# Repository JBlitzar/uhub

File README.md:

# uhub

> [!NOTE]
> uhh so the ports are very close together, which means for some thick USB connectors, plugging in to ports that are next to each other won't work. You might want to space them out if youre going to fab this yourself. Or, you know, just live with it and use skinny connectors.

## Finished product

## other pictures

## What this project is and why I made it

It's a USB hub. It has one upstream USB-C port, and seven downstream ports: Five USB-A and two USB-C. Since the ICs only support four downstream ports, I daisy-chained two of them.

I wanted to make it to connect to more accessories at a time, for use either on my laptop or with my raspberry pi. I also wanted to make it to level up my PCB design skills, after making a macropad. The routing was considerably more difficult, because there a lot more considerations to be made regarding impedance et al.

## PCB Images

[KiCanvas](https://kicanvas.org/?repo=https%3A%2F%2Fgithub.com%2FJBlitzar%2Fuhub%2Ftree%2Fmain%2FPCB%2Fusbhub)

For-fun PCB plot, kicad screenshots below.

## Credits

USB Hub Guide: https://rudymakes.com/blog/usb-hub/

I'd like to credit this guide, since I used it as reference, but my design is distinct and my own.

## Bom in table format

| Name            | Link                                              | Footprint                        | Quantity | Value            | LCSC Part # | Designator                                                    | Distributor  | Total cost |
| --------------- | ------------------------------------------------- | -------------------------------- | -------- | ---------------- | ----------- | ------------------------------------------------------------- | ------------ | ---------- |
| 1uF capacitor   | https://www.lcsc.com/product-detail/C29266.html   | C0402                            | 13       | 1uF              | C29266      | C11, C13, C15, C17, C19, C20, C21, C22, C23, C24, C25, C7, C9 | LCSC         | 0          |
| 100nF capacitor | https://www.lcsc.com/product-detail/C60474.html   | C0402                            | 6        | 100nF            | C60474      | C12, C14, C16, C18, C26, C27                                  | LCSC         | 0          |
| 5.1k resistor   | https://www.lcsc.com/product-detail/C105872.html  | R0402                            | 6        | 5.1k             | C105872     | R10, R11, R4, R7, R8, R9                                      | LCSC         | 0          |
| USB IC          | https://www.lcsc.com/product-detail/C2684433.html | SSOP-16_L4.6-W2.6-P0.53-LS4.0-BL | 2        | SL2.1S           | C2684433    | U1, U2                                                        | LCSC         | 0          |
| USB C port      | https://www.lcsc.com/product-detail/C2765186.html | USB-C-SMD_TYPE-C-16PIN-2MD-073   | 3        | TYPE-C 16PIN 2MD | C2765186    | USB1_UPSTREAM1, USB5, USB6                                    | LCSC         | 0          |
| USB A port      | https://www.lcsc.com/product-detail/C668591.html  | USB-A-TH_10.0QHHTZB6.3           | 5        | 10.0 QHHTZB6.3   | C668591     | USB2, USB3, USB4, USB7, USB8                                  | LCSC         | 0          |
| PCB             | N/A                                               | N/A                              | 1        | N/A              | N/A         | N/A                                                           | JLCPCB       | 4          |
| PCBA            | N/A                                               | N/A                              | 1        | N/A              | N/A         | N/A                                                           | JLCPCB       | 32.78      |
| Shipping        | N/A                                               | N/A                              | 1        | N/A              | N/A         | N/A                                                           | JLCPCB       | 3.3        |
| Sales tax       | N/A                                               | N/A                              | 1        | N/A              | N/A         | N/A                                                           | JLCPCB       | 4          |
| 3d printed case | N/A                                               | N/A                              | 1        | N/A              | N/A         | N/A                                                           | self-sourced | 0          |

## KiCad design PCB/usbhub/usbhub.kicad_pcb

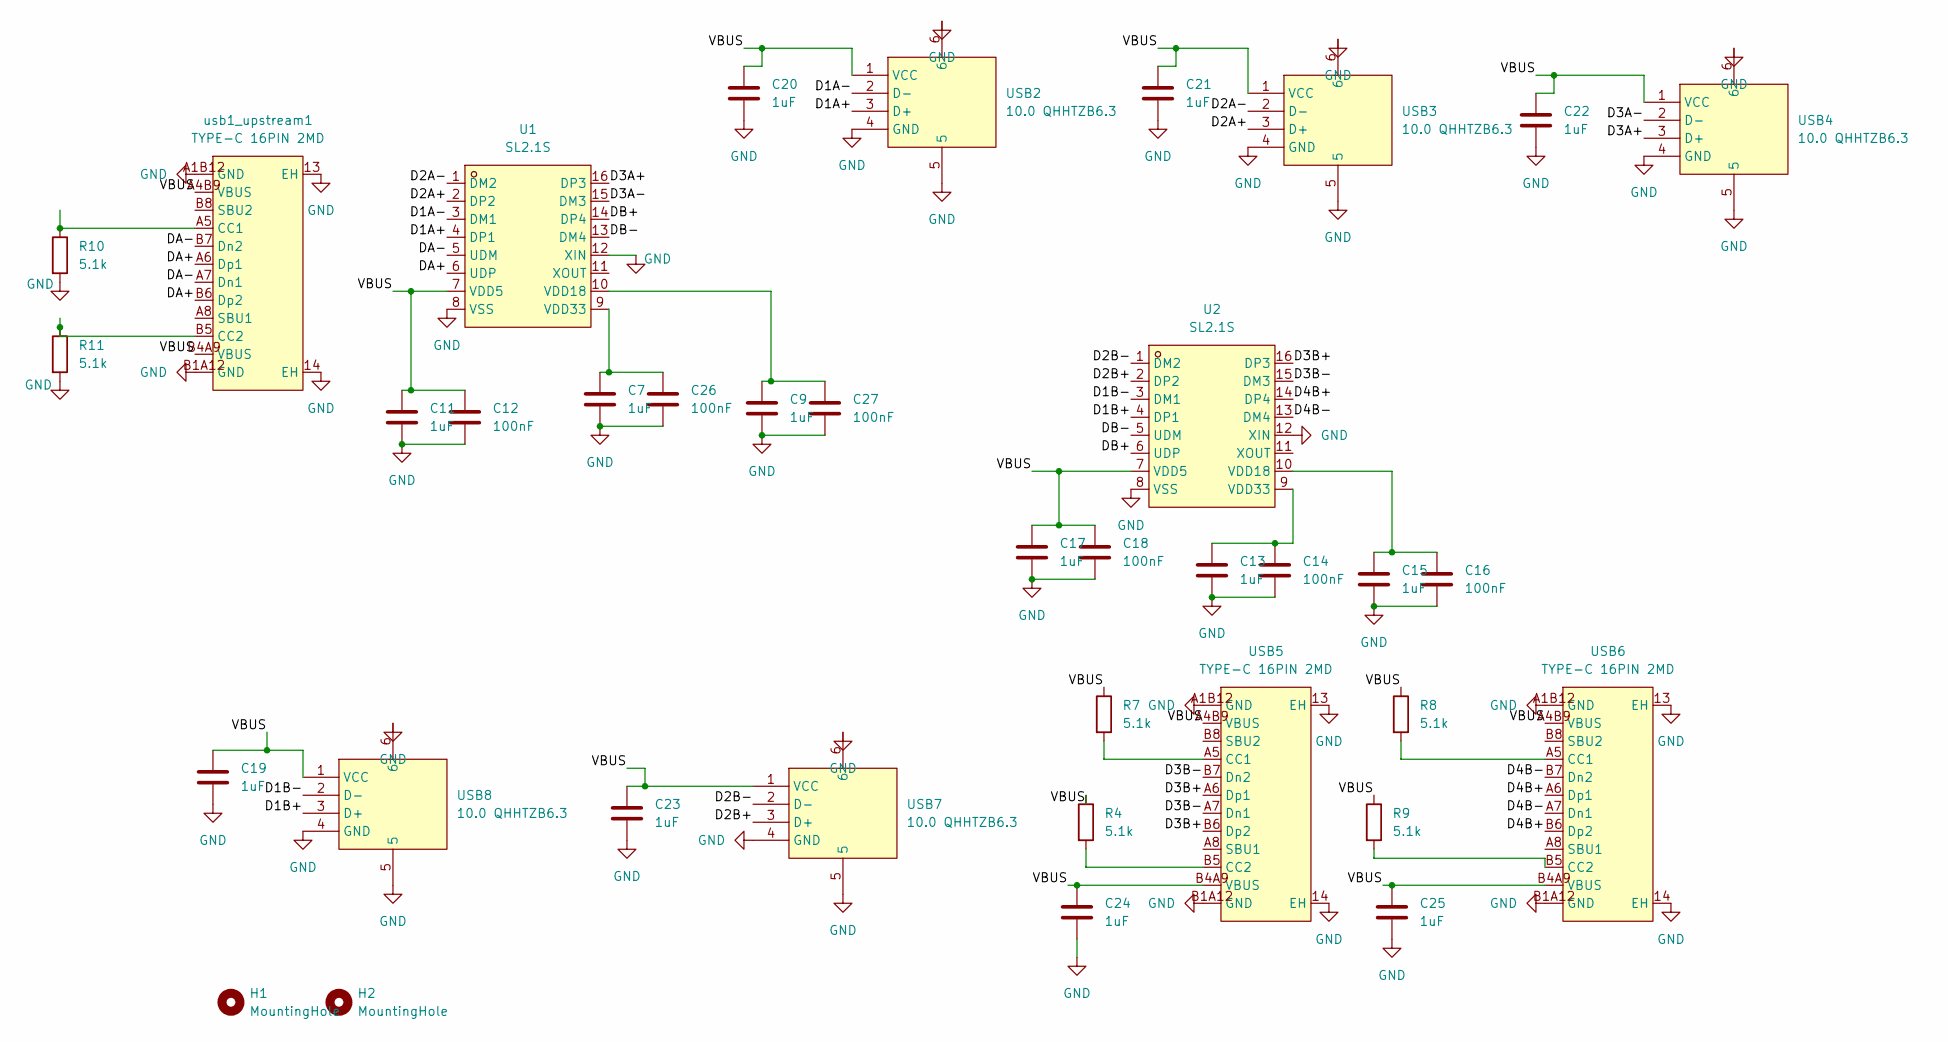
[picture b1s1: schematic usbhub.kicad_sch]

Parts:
C7, C9, C11, C13, C15, C17, C19, C20, C21, C22, C23, C24, C25: 1uF; C0402; LCSC Part C29266
C12, C14, C16, C18, C26, C27: 100nF; C0402; LCSC Part C60474
H1, H2: MountingHole; MountingHole_3.2mm_M3
R4, R7, R8, R9, R10, R11: 5.1k; R0402; LCSC Part C105872
U1, U2: SL2.1S; SSOP-16_L4.6-W2.6-P0.53-LS4.0-BL; MPN SL2.1s; LCSC Part C2684433
USB2, USB3, USB4, USB7, USB8: 10.0 QHHTZB6.3; USB-A-TH_10.0QHHTZB6.3; MPN 10.0 QHHTZB6.3; LCSC Part C668591
USB5, USB6: TYPE-C 16PIN 2MD; USB-C-SMD_TYPE-C-16PIN-2MD-073; MPN TYPE-C 16PIN 2MD(073); LCSC Part C2765186
usb1_upstream1: TYPE-C 16PIN 2MD; USB-C-SMD_TYPE-C-16PIN-2MD-073; MPN TYPE-C 16PIN 2MD(073); LCSC Part C2765186

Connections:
/D1A+: U1.4 (DP1), USB2.3 (D+)
/D1A-: U1.3 (DM1), USB2.2 (D-)
/D1B+: U2.4 (DP1), USB8.3 (D+)
/D1B-: U2.3 (DM1), USB8.2 (D-)
/D2A+: U1.2 (DP2), USB3.3 (D+)
/D2A-: U1.1 (DM2), USB3.2 (D-)
/D2B+: U2.2 (DP2), USB7.3 (D+)
/D2B-: U2.1 (DM2), USB7.2 (D-)
/D3A+: U1.16 (DP3), USB4.3 (D+)
/D3A-: U1.15 (DM3), USB4.2 (D-)
/D3B+: U2.16 (DP3), USB5.A6 (Dp1), USB5.B6 (Dp2)
/D3B-: U2.15 (DM3), USB5.A7 (Dn1), USB5.B7 (Dn2)
/D4B+: U2.14 (DP4), USB6.A6 (Dp1), USB6.B6 (Dp2)
/D4B-: U2.13 (DM4), USB6.A7 (Dn1), USB6.B7 (Dn2)
/DA+: U1.6 (UDP), usb1_upstream1.A6 (Dp1), usb1_upstream1.B6 (Dp2)
/DA-: U1.5 (UDM), usb1_upstream1.A7 (Dn1), usb1_upstream1.B7 (Dn2)
/DB+: U1.14 (DP4), U2.6 (UDP)
/DB-: U1.13 (DM4), U2.5 (UDM)
/VBUS: C11.1, C12.1, C17.1, C18.1, C19.1, C20.1, C21.1, C22.1, C23.1, C24.1, C25.1, R4.1, R7.1, R8.1, R9.1, U1.7 (VDD5), U2.7 (VDD5), USB2.1 (VCC), USB3.1 (VCC), USB4.1 (VCC), USB5.A4B9 (VBUS), USB5.B4A9 (VBUS), USB6.A4B9 (VBUS), USB6.B4A9 (VBUS), USB7.1 (VCC), USB8.1 (VCC), usb1_upstream1.A4B9 (VBUS), usb1_upstream1.B4A9 (VBUS)
GND: C7.2, C9.2, C11.2, C12.2, C13.2, C14.2, C15.2, C16.2, C17.2, C18.2, C19.2, C20.2, C21.2, C22.2, C23.2, C24.2, C25.2, C26.2, C27.2, R10.2, R11.2, U1.8 (VSS), U1.12 (XIN), U2.8 (VSS), U2.12 (XIN), USB2.4 (GND), USB2.5, USB2.6, USB3.4 (GND), USB3.5, USB3.6, USB4.4 (GND), USB4.5, USB4.6, USB5.13 (EH), USB5.14 (EH), USB5.A1B12 (GND), USB5.B1A12 (GND), USB6.13 (EH), USB6.14 (EH), USB6.A1B12 (GND), USB6.B1A12 (GND), USB7.4 (GND), USB7.5, USB7.6, USB8.4 (GND), USB8.5, USB8.6, usb1_upstream1.13 (EH), usb1_upstream1.14 (EH), usb1_upstream1.A1B12 (GND), usb1_upstream1.B1A12 (GND)
unnamed: C9.1, C27.1, U1.10 (VDD18)
unnamed: C7.1, C26.1, U1.9 (VDD33)
unnamed: C15.1, C16.1, U2.10 (VDD18)
unnamed: C13.1, C14.1, U2.9 (VDD33)
unnamed: R7.2, USB5.A5 (CC1)
unnamed: R4.2, USB5.B5 (CC2)
unnamed: R8.2, USB6.A5 (CC1)
unnamed: R9.2, USB6.B5 (CC2)
unnamed: R10.1, usb1_upstream1.A5 (CC1)
unnamed: R11.1, usb1_upstream1.B5 (CC2)

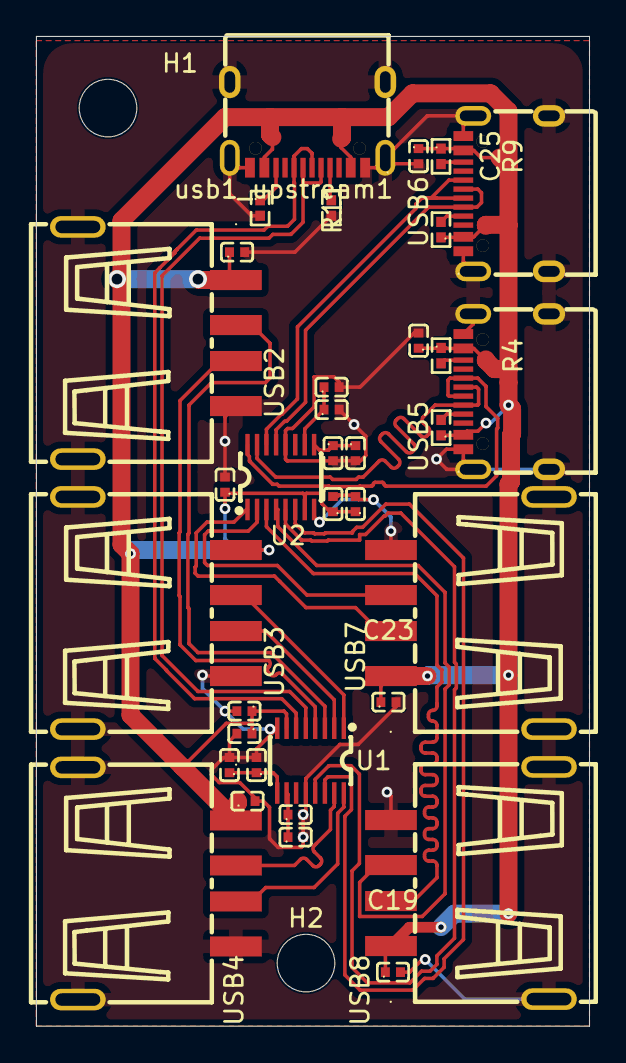
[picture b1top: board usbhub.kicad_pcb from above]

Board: 2 copper layers, 30.7 x 55.0 mm, 37 parts (0 on the bottom side), 30 nets.

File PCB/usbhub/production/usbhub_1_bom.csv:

Designator,Footprint,Quantity,Value,LCSC Part #
"C11, C13, C15, C17, C19, C20, C21, C22, C23, C24, C25, C7, C9",C0402,13,1uF,C29266
"C12, C14, C16, C18, C26, C27",C0402,6,100nF,C60474
"R10, R11, R4, R7, R8, R9",R0402,6,5.1k,C105872
"U1, U2",SSOP-16_L4.6-W2.6-P0.53-LS4.0-BL,2,SL2.1S,C2684433
"USB1_UPSTREAM1, USB5, USB6",USB-C-SMD_TYPE-C-16PIN-2MD-073,3,TYPE-C 16PIN 2MD,C2765186
"USB2, USB3, USB4, USB7, USB8",USB-A-TH_10.0QHHTZB6.3,5,10.0 QHHTZB6.3,C668591

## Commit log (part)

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2026-05-09 A preliminary schematic
2026-05-09 unmixup cc1 with sbu1
2026-05-09 minus/plus rename
2026-05-09 placement
2026-05-09 routing? idk bro
2026-05-10 route it lwk
2026-05-10 some skew tweaks
2026-05-10 length match everything nicer
2026-05-10 better silkscreen
2026-05-10 renders
2026-05-10 case and assembly
2026-05-10 just the production files
2026-05-10 docs!!
2026-05-10 new bom
2026-05-10 Production files
2026-05-26 note
2026-05-27 update all the steps
2026-05-27 make it 6mm
2026-05-27 no curvy trace around nonexistent hole
2026-05-31 tune skew, eliminate via-in-pad, improve gnd connections
2026-05-31 refab
2026-06-04 final
2026-06-04 jouranl
2026-06-29 the real image
2026-06-30 vdieo
